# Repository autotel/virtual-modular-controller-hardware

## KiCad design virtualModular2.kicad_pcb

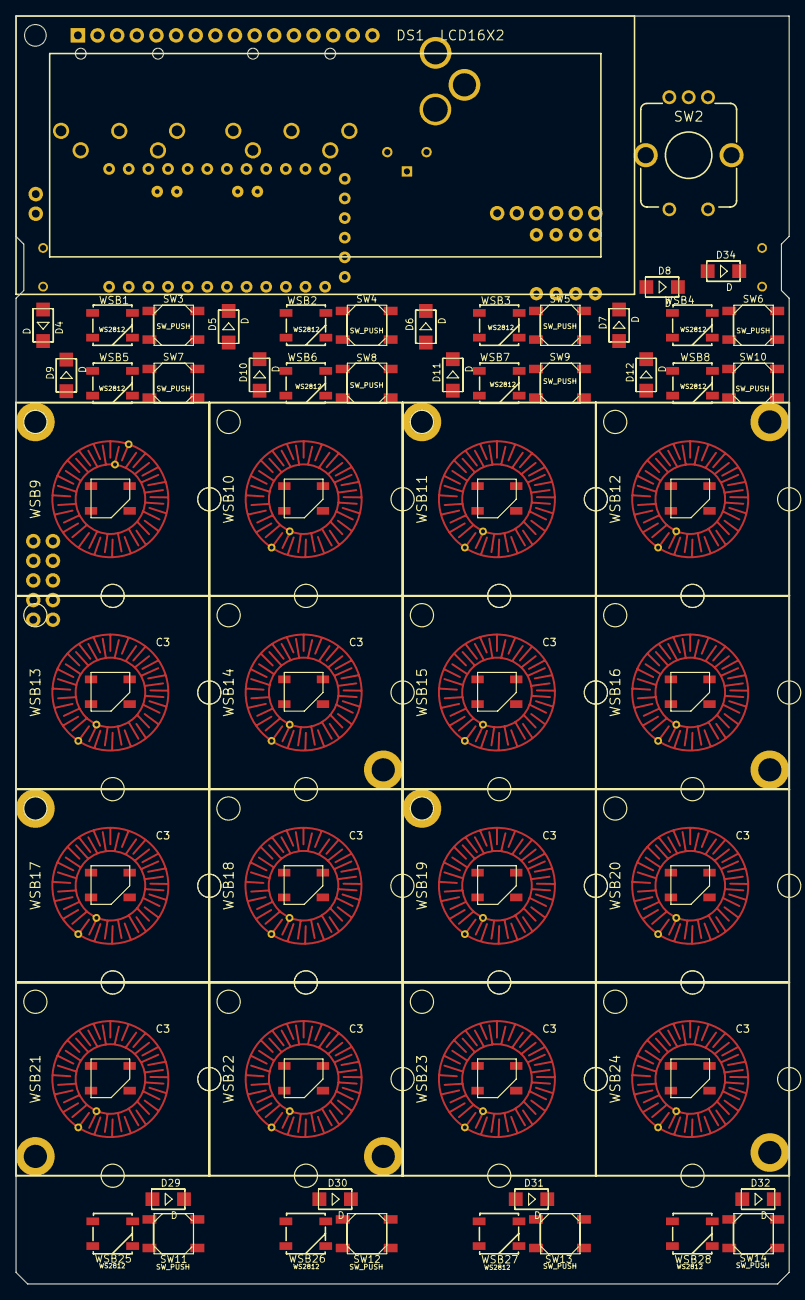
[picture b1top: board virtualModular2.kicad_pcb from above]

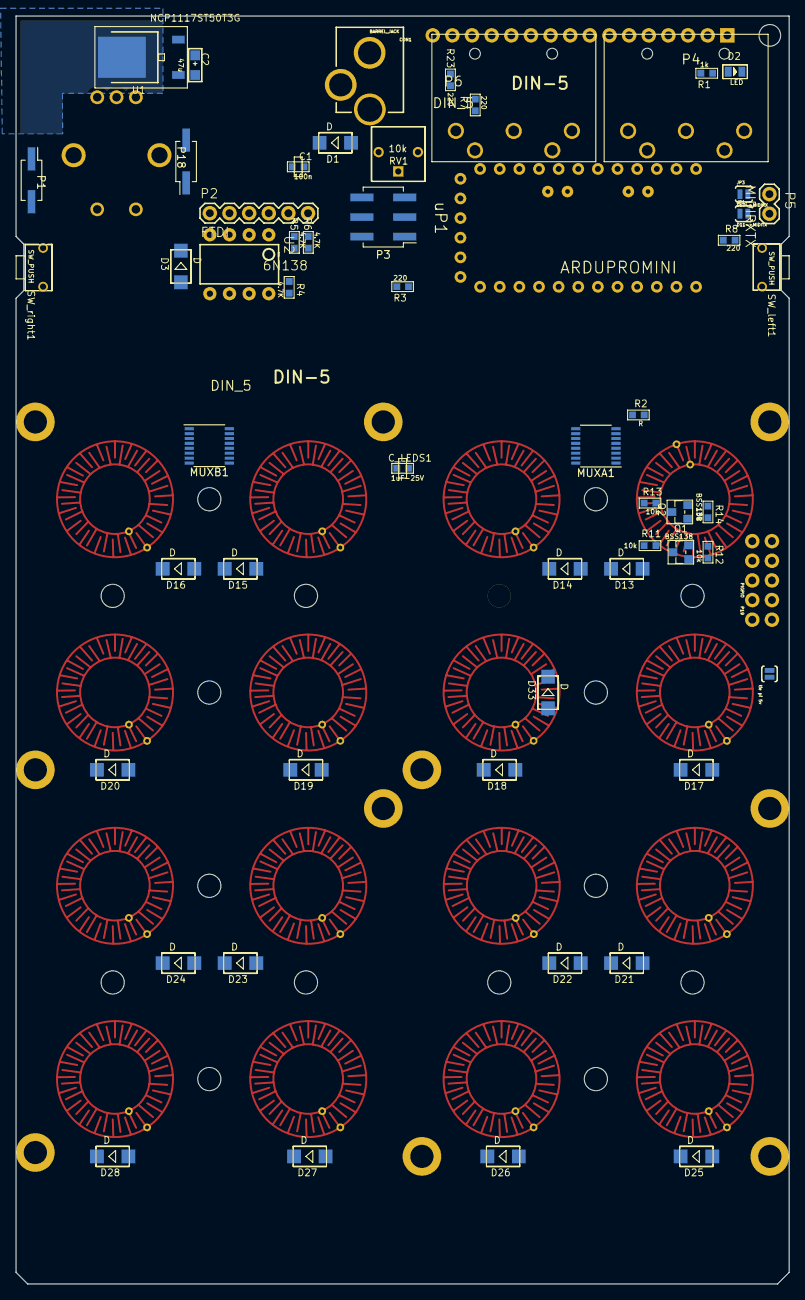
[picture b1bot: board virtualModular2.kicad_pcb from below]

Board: 2 copper layers, 100.0 x 164.0 mm, 138 parts (58 on the bottom side), 114 nets, no tracks yet.

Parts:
C1: 100n; C0603
C2: 47u; AVX-A
CON1: BARREL_JACK; POWER_JACK_PTH_LOCK
C_LEDS1: 1uF-25V; C0603
D1, D3, D4, D5, D6, D7, D8, D9, D10, D11, D12, D13, D14, D15, D16, D17, D18, D19, D20, D21, D22, D23, D24, D25, D26, D27, D28, D29, D30, D31, D32, D33, D34: D; DO-214AC
D2: LED; LED-0805
DS1: LCD16X2; LCD-16X2
HOLE00, HOLE01, HOLE02, HOLE03, HOLE04, HOLE05, HOLE06, HOLE07, HOLE08, HOLE09, HOLE10, HOLE11, HOLE12, HOLE13, HOLE14, HOLE15, HOLE16, HOLE17, HOLE18, HOLE19, HOLE20, HOLE21, HOLE22, HOLE23: MountingHole_3mm
JP1: D11->MIDITX; PAD-JUMPER-2-NC_BY_TRACE_YES_SILK
JP2: tie pi 5v; PAD-JUMPER-2-NO_YES_SILK
JP3: D10->MIDIRX; PAD-JUMPER-2-NC_BY_TRACE_YES_SILK
MUXA1: 4051; SSOP-16_3.9x4.9mm_Pitch0.635mm
MUXB1: 4051; SSOP-16_3.9x4.9mm_Pitch0.635mm
P1: POWER; Pin_Header_Straight_2x01_Pitch2.54mm_SMD
P2: FTDI; 1X06
P3: 5V SPI; Pin_Header_Straight_2x03_Pitch2.54mm_SMD
P4, P6: DIN_5; DIN_5_FEMALE
P5: MIDIRXTX; 1X02
P18: 3VI2C; Pin_Header_Straight_2x01_Pitch2.54mm_SMD
P19: PIGPIO; 2X5_NOSILK
Q1, Q2: BSS138; SOT-23
R1: 1k; R0603
R2: R; R0603
R3, R7, R8, R23: 220; R0603
R4, R5, R6: 4.7K; R0603
R11, R12, R13, R14: 10k; R0603
RV1: 10k; trimpot
SW2: ROTARY_ENCODER_SWITCH; ENCODER_LED_2
SW3, SW4, SW5, SW6, SW7, SW8, SW9, SW10, SW11, SW12, SW13, SW14: SW_PUSH; SW4-SMD-5.2X5.2X1.5MM
SW_left1: SW_PUSH; SW2-5.0-6.0X3.0X4.3MM
SW_right1: SW_PUSH; SW2-5.0-6.0X3.0X4.3MM
U1: NCP1117ST50T3G; TO-252
U2: 6N138; DIP08
WSB1, WSB2, WSB3, WSB4, WSB5, WSB6, WSB7, WSB8, WSB25, WSB26, WSB27, WSB28: WS2812; WS2812B
WSB9, WSB10, WSB11, WSB12, WSB13, WSB14, WSB15, WSB16, WSB17, WSB18, WSB19, WSB20, WSB21, WSB22, WSB23, WSB24: WS2812_BUTTON; ws2812_buttonPad
uP1: ARDUPROMINI; ArduProMini

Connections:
+5V: C_LEDS1.1, DS1.2, JP2.2, MUXA1.16, MUXB1.16, P1.2, P2.3, P3.2, R1.1, R5.1, R7.1, R11.2, R13.2, R23.1, RV1.1, U1.2, U2.8, WSB1.1, WSB2.1, WSB3.1, WSB4.1, WSB5.1, WSB6.1, WSB7.1, WSB8.1, WSB9.1, WSB10.1, WSB11.1, WSB12.1, WSB13.1, WSB14.1, WSB15.1, WSB16.1, WSB17.1, WSB18.1, WSB19.1, WSB20.1, WSB21.1, WSB22.1, WSB23.1, WSB24.1, WSB25.1, WSB26.1, WSB27.1, WSB28.1, uP1.3
/3vRX0: P19.9, Q1.2, R12.2
/3vTX0: P19.7, Q2.2, R14.2
/ENCA: SW2.A, uP1.33
/ENCC: SW2.B, uP1.34
/LCD0: DS1.4, uP1.18
/LCD1: DS1.6, uP1.28
/LCD2: DS1.11, uP1.27
/LCD3: DS1.12, uP1.26
/LCD4: DS1.13, uP1.25
/LCD5: DS1.14, uP1.24
/MIDI_RX: JP3.2, P5.1, R6.2
/MIDI_TX: JP1.2, P5.2, R8.1
/MUXAADDR0: MUXA1.11, uP1.11
/MUXAADDR1: MUXA1.10, uP1.12
/MUXAADDR2: MUXA1.9, uP1.13
/MUXAX0: MUXA1.13, SW3.2, SW7.2, SW11.2, WSB9.6, WSB13.6, WSB17.6, WSB21.6
/MUXAX1: MUXA1.14, SW4.2, SW8.2, SW12.2, WSB10.6, WSB14.6, WSB18.6, WSB22.6
/MUXAX2: MUXA1.15, SW5.2, SW9.2, SW13.2, WSB11.6, WSB15.6, WSB19.6, WSB23.6
/MUXAX3: MUXA1.12, SW6.2, SW10.2, SW14.2, WSB12.6, WSB16.6, WSB20.6, WSB24.6
/MUXAX4: MUXA1.1, SW2.D, SW_left1.2, SW_right1.2
/MUXA_COMMON: MUXA1.3, R2.2, uP1.32
/MUXBADDR0: MUXB1.11, uP1.14
/MUXBADDR1: MUXB1.10, uP1.15
/MUXBADDR2: MUXB1.9, uP1.16
/MUXBX0: D4.1, D5.1, D6.1, D7.1, D8.1, MUXB1.13
/MUXBX1: D9.1, D10.1, D11.1, D12.1, D33.1, MUXB1.14
/MUXBX2: D13.1, D14.1, D15.1, D16.1, D34.1, MUXB1.15
/MUXBX3: D17.1, D18.1, D19.1, D20.1, MUXB1.12
/MUXBX4: D21.1, D22.1, D23.1, D24.1, MUXB1.1
/MUXBX5: D25.1, D26.1, D27.1, D28.1, MUXB1.5
/MUXBX6: D29.1, D30.1, D31.1, D32.1, MUXB1.2
/MUXB_COMMON: MUXB1.3, uP1.31
/PI5vRX0: P2.4, Q1.3, R11.1, uP1.4
/PI5vTX0: P2.5, Q2.3, R13.1, uP1.5
/PI_3V3: P19.2, Q1.1, Q2.1, R12.1, R14.1
/PI_5V: JP2.1, P19.1, P19.3
/PI_SCL: P18.1, P19.6
/PI_SDA: P18.2, P19.4
/RESET: P2.6, P3.5, uP1.6
/SERIAL_LED_PIN: WSB1.4, uP1.17
/SERIAL_LED_TOROW_1: WSB4.2, WSB5.4
/SERIAL_LED_TOROW_2: WSB8.2, WSB9.4
/SERIAL_LED_TOROW_3: WSB12.2, WSB13.4
/SERIAL_LED_TOROW_4: WSB16.2, WSB17.4
/SERIAL_LED_TOROW_5: WSB20.2, WSB21.4
/SERIAL_LED_TOROW_6: WSB24.2, WSB25.4
GND: C1.2, C2.-, CON1.GND, C_LEDS1.2, D2.-, DS1.1, DS1.5, DS1.16, MUXA1.6, MUXA1.7, MUXA1.8, MUXB1.6, MUXB1.7, MUXB1.8, P1.1, P2.1, P2.2, P3.6, P6.2, P19.5, P19.10, R2.1, R4.1, RV1.3, SW2.C, U1.1, U2.5, WSB1.3, WSB2.3, WSB3.3, WSB4.3, WSB5.3, WSB6.3, WSB7.3, WSB8.3, WSB9.3, WSB10.3, WSB11.3, WSB12.3, WSB13.3, WSB14.3, WSB15.3, WSB16.3, WSB17.3, WSB18.3, WSB19.3, WSB20.3, WSB21.3, WSB22.3, WSB23.3, WSB24.3, WSB25.3, WSB26.3, WSB27.3, WSB28.3, uP1.1, uP1.2
unnamed: C1.1, C2.+, D1.2, U1.3
unnamed: CON1.PWR, D1.1
unnamed: D2.+, R1.2
unnamed: D3.1, P4.5, U2.3
unnamed: D3.2, R3.1, U2.2
unnamed: D4.2, SW3.1
unnamed: D5.2, SW4.1
unnamed: D6.2, SW5.1
unnamed: D7.2, SW6.1
unnamed: D8.2, SW2.E
unnamed: D9.2, SW7.1
unnamed: D10.2, SW8.1
unnamed: D11.2, SW9.1
unnamed: D12.2, SW10.1
unnamed: D13.2, WSB9.5
unnamed: D14.2, WSB10.5
unnamed: D15.2, WSB11.5
unnamed: D16.2, WSB12.5
unnamed: D17.2, WSB13.5
unnamed: D18.2, WSB14.5
unnamed: D19.2, WSB15.5
unnamed: D20.2, WSB16.5
unnamed: D21.2, WSB17.5
unnamed: D22.2, WSB18.5
unnamed: D23.2, WSB19.5
unnamed: D24.2, WSB20.5
unnamed: D25.2, WSB21.5
unnamed: D26.2, WSB22.5
unnamed: D27.2, WSB23.5
unnamed: D28.2, WSB24.5
unnamed: D29.2, SW11.1
unnamed: D30.2, SW12.1
unnamed: D31.2, SW13.1
unnamed: D32.2, SW14.1
unnamed: D33.2, SW_left1.1
unnamed: D34.2, SW_right1.1
unnamed: DS1.3, RV1.2
unnamed: DS1.15, R23.2
unnamed: JP1.1, uP1.29
unnamed: JP3.1, uP1.30
unnamed: P4.4, R3.2
unnamed: P6.4, R7.2
unnamed: P6.5, R8.2
unnamed: R4.2, U2.7
unnamed: R5.2, R6.1, U2.6
unnamed: WSB1.2, WSB2.4
unnamed: WSB2.2, WSB3.4
unnamed: WSB3.2, WSB4.4
unnamed: WSB5.2, WSB6.4
unnamed: WSB6.2, WSB7.4
unnamed: WSB7.2, WSB8.4
unnamed: WSB10.2, WSB11.4
unnamed: WSB9.2, WSB10.4
unnamed: WSB11.2, WSB12.4
unnamed: WSB13.2, WSB14.4
unnamed: WSB14.2, WSB15.4
unnamed: WSB15.2, WSB16.4
unnamed: WSB17.2, WSB18.4
unnamed: WSB18.2, WSB19.4
unnamed: WSB19.2, WSB20.4
unnamed: WSB21.2, WSB22.4
unnamed: WSB22.2, WSB23.4
unnamed: WSB23.2, WSB24.4
unnamed: WSB25.2, WSB26.4
unnamed: WSB26.2, WSB27.4
unnamed: WSB27.2, WSB28.4

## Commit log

2017-09-11 init
2017-09-17 details in layout etc
2017-09-18 PIGPIO was right over a button pad
2017-09-18 repositioning some items
2017-09-27 Add pulldown resistor to MUXA, and test routing, small changes
2017-10-01 shematic addition of midi io (to be an optional later)
2017-10-01 add midi io to the board
